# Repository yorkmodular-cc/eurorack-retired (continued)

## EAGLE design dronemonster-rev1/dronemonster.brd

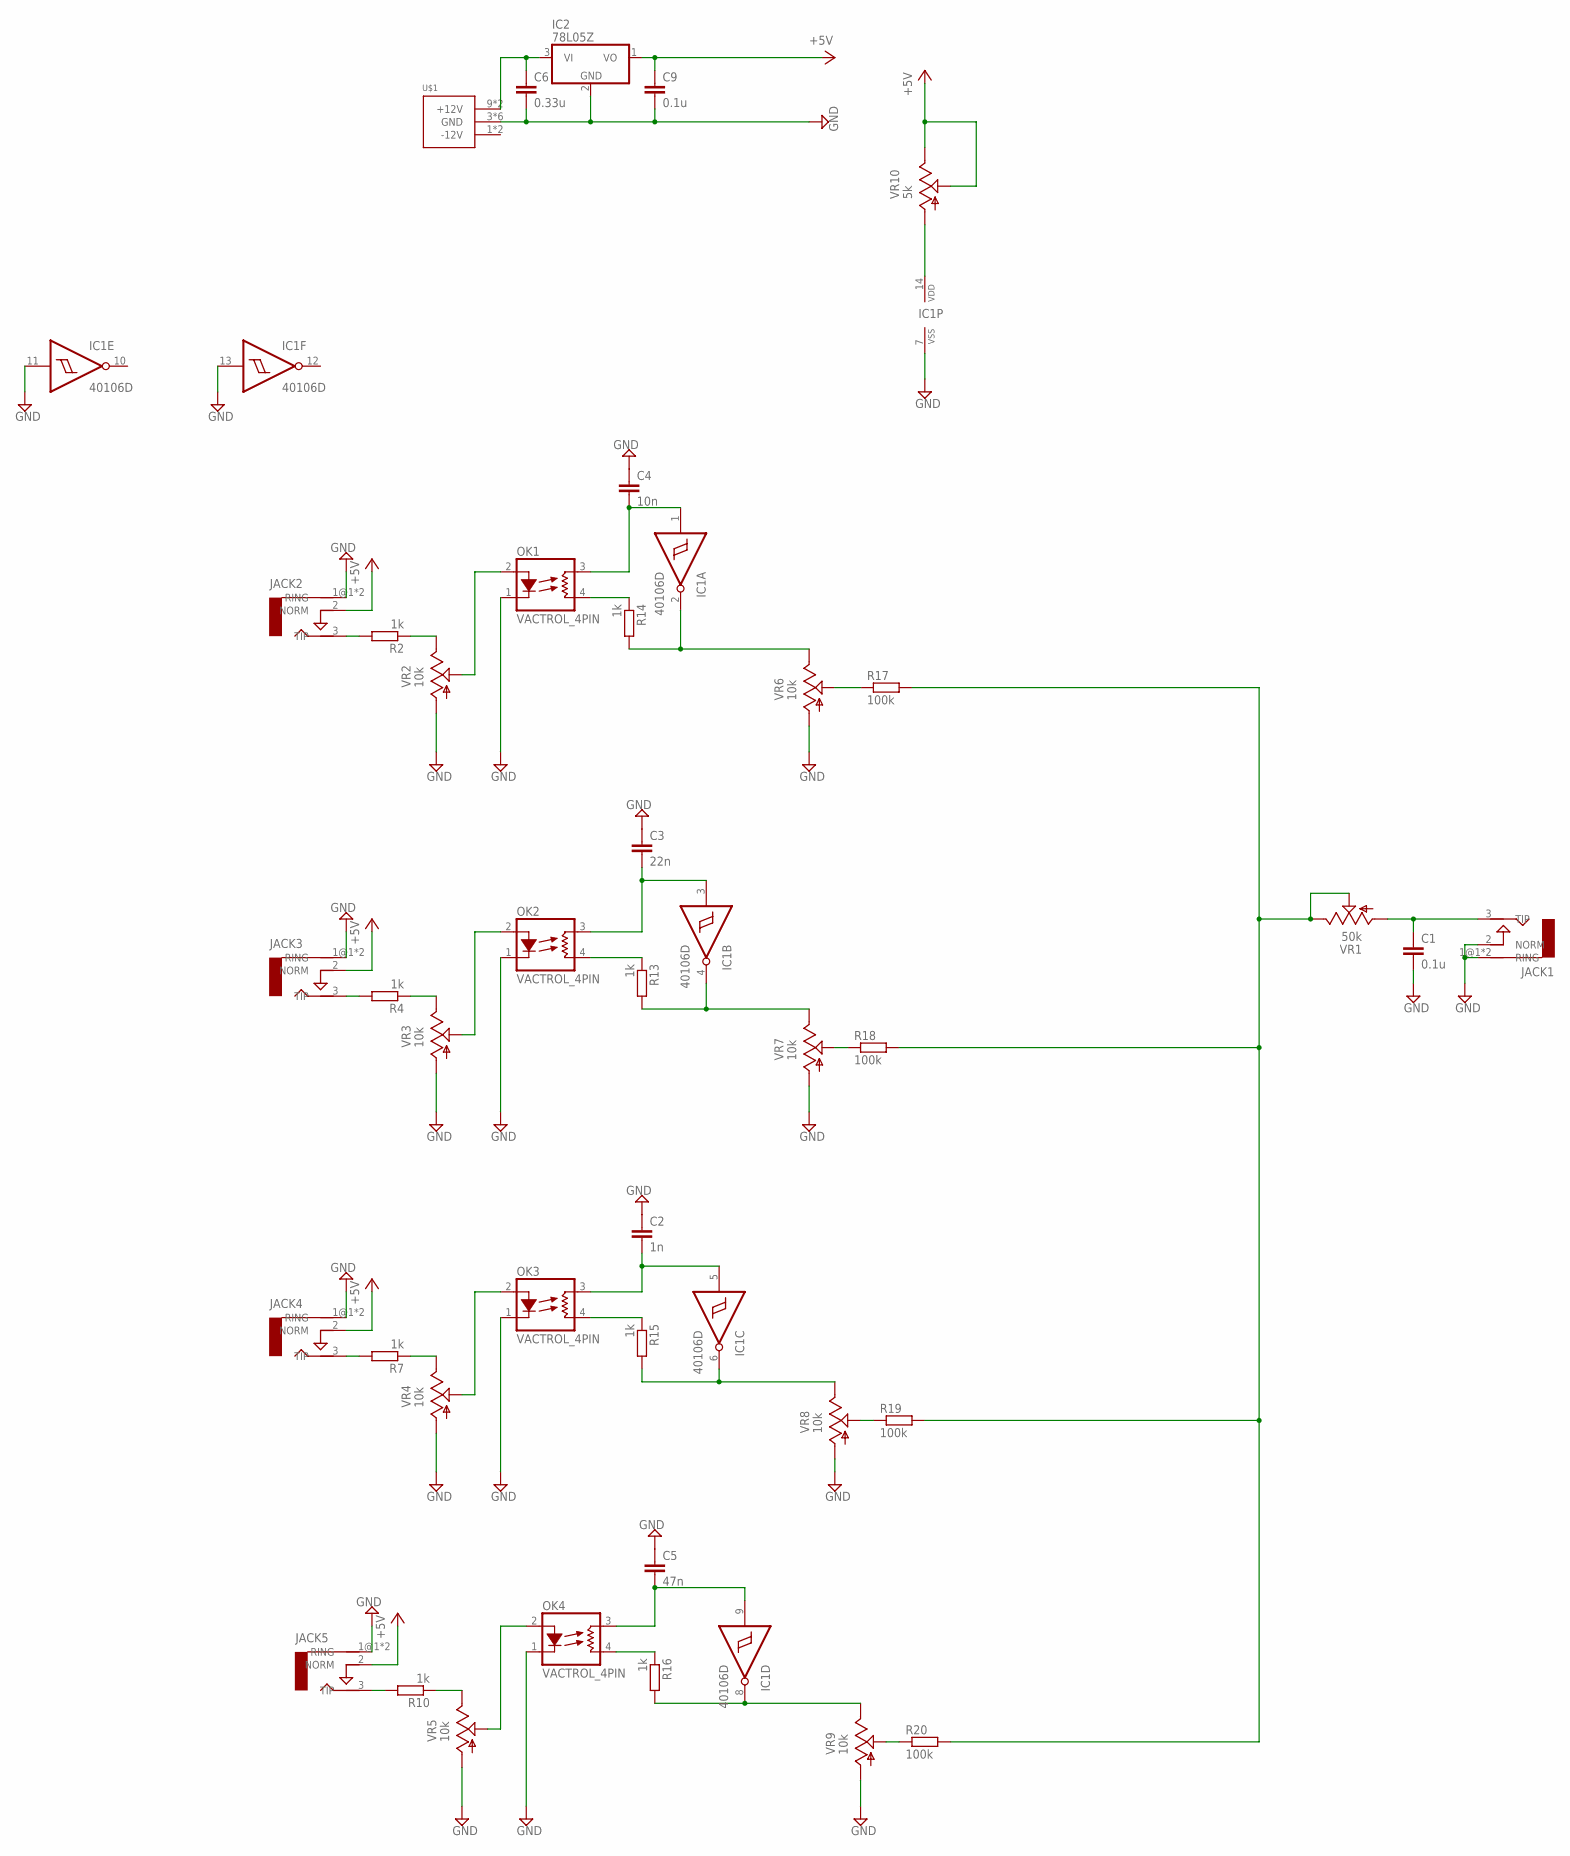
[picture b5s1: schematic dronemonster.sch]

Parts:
C1: 0.1u; C050-025X075
C2: 1n; C050-025X075
C3: 22n; C050-025X075
C4: 10n; C050-025X075
C5: 47n; C050-025X075
C6: 0.33u; C0805
C9: 0.1u; C0805
IC1: 40106D; SO14
IC2: 78L05Z; TO92
JACK1, JACK2, JACK3, JACK4, JACK5: AUDIO-JACKERTHENVAR; ERTHENVAR-JACK
OK1, OK2, OK3, OK4: VACTROL_4PIN; VACTROL_4PIN_VTL5C
R2, R4, R7, R10, R13, R14, R15, R16: 1k; R0805
R17, R18, R19, R20: 100k; R0805
U$1: POWER_SIMPLE10; POWER_10
VR1: 50k; 9MM_SNAP-IN_POT
VR2, VR3, VR4, VR5, VR6, VR7, VR8, VR9: 10k; 9MM_SNAP-IN_POT
VR10: 5k; 9MM_SNAP-IN_POT

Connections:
+5V: C9.1, IC2.1 (VO), JACK2.2 (NORM), JACK3.2 (NORM), JACK4.2 (NORM), JACK5.2 (NORM), VR10.2 (S), VR10.3 (E)
GND: C1.2, C2.1, C3.1, C4.1, C5.1, C6.2, C9.2, IC1.7 (VSS), IC1.11 (I), IC1.13 (I), IC2.2 (GND), JACK1.1@1 (RING), JACK1.1@2 (RING), JACK1.2 (NORM), JACK2.1@1 (RING), JACK2.1@2 (RING), JACK3.1@1 (RING), JACK3.1@2 (RING), JACK4.1@1 (RING), JACK4.1@2 (RING), JACK5.1@1 (RING), JACK5.1@2 (RING), OK1.1 (LED-), OK2.1 (LED-), OK3.1 (LED-), OK4.1 (LED-), U$1.3 (GND), U$1.4 (GND), U$1.5 (GND), U$1.6 (GND), U$1.7 (GND), U$1.8 (GND), VR2.1 (A), VR3.1 (A), VR4.1 (A), VR5.1 (A), VR6.1 (A), VR7.1 (A), VR8.1 (A), VR9.1 (A)
unnamed: C1.1, JACK1.3 (TIP), VR1.1 (A)
unnamed: IC1.14 (VDD), VR10.1 (A)
unnamed: JACK2.3 (TIP), R2.2
unnamed: OK1.2 (LED+), VR2.2 (S)
unnamed: R2.1, VR2.3 (E)
unnamed: R4.1, VR3.3 (E)
unnamed: JACK3.3 (TIP), R4.2
unnamed: OK2.2 (LED+), VR3.2 (S)
unnamed: R7.1, VR4.3 (E)
unnamed: JACK4.3 (TIP), R7.2
unnamed: OK3.2 (LED+), VR4.2 (S)
unnamed: R10.1, VR5.3 (E)
unnamed: JACK5.3 (TIP), R10.2
unnamed: OK4.2 (LED+), VR5.2 (S)
unnamed: R20.1, VR9.2 (S)
unnamed: R19.1, VR8.2 (S)
unnamed: OK4.4 (RES2), R16.1
unnamed: IC1.8 (O), R16.2, VR9.3 (E)
unnamed: C5.2, IC1.9 (I), OK4.3 (RES1)
unnamed: OK3.4 (RES2), R15.1
unnamed: IC1.6 (O), R15.2, VR8.3 (E)
unnamed: C2.2, IC1.5 (I), OK3.3 (RES1)
unnamed: OK2.4 (RES2), R13.1
unnamed: IC1.4 (O), R13.2, VR7.3 (E)
unnamed: C3.2, IC1.3 (I), OK2.3 (RES1)
unnamed: OK1.4 (RES2), R14.1
unnamed: IC1.2 (O), R14.2, VR6.3 (E)
unnamed: C4.2, IC1.1 (I), OK1.3 (RES1)
unnamed: R18.1, VR7.2 (S)
unnamed: C6.1, IC2.3 (VI), U$1.9 (+12V), U$1.10 (+12V)
unnamed: R17.1, VR6.2 (S)
OSC4: R17.2, R18.2, R19.2, R20.2, VR1.2 (S), VR1.3 (E)

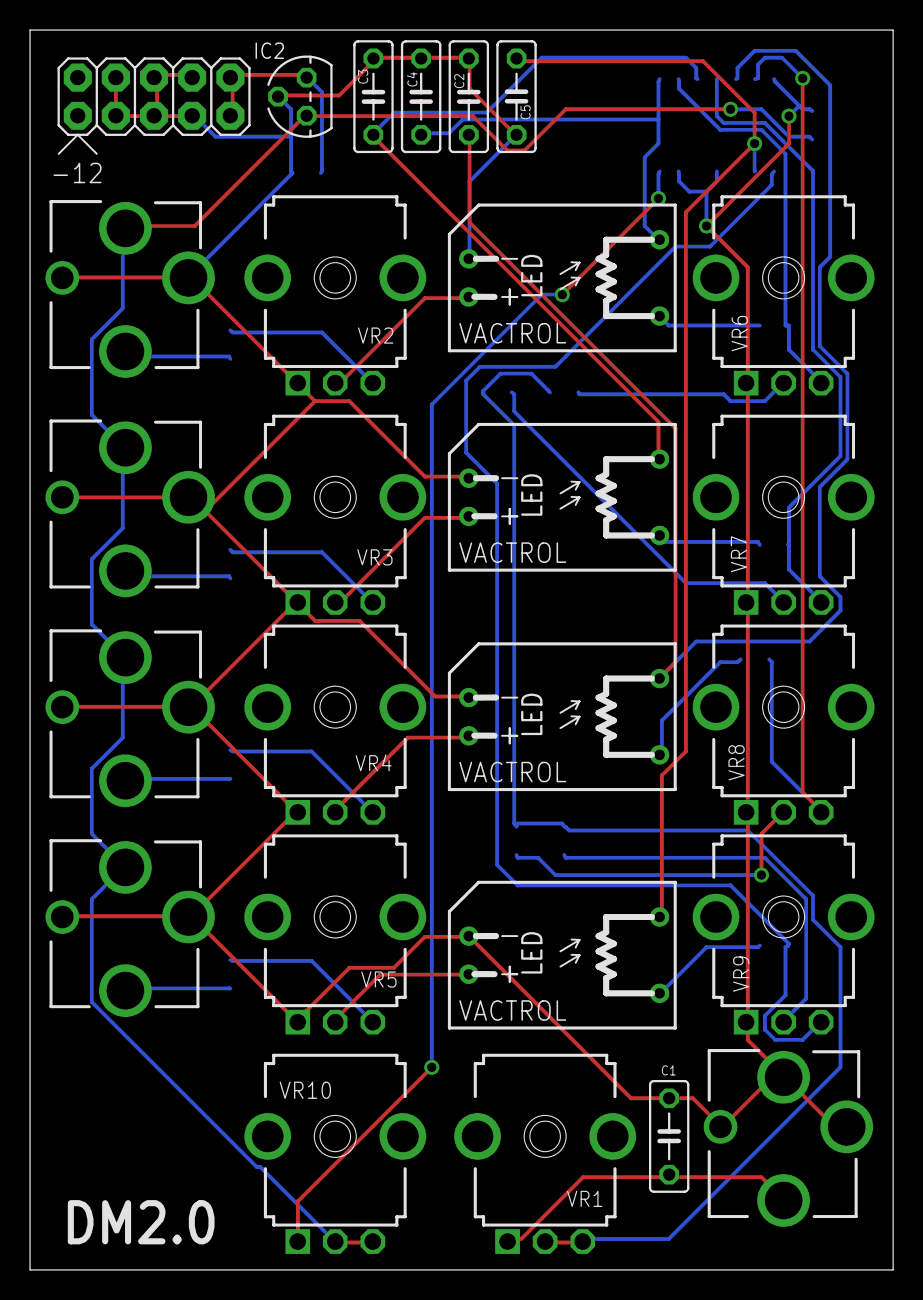
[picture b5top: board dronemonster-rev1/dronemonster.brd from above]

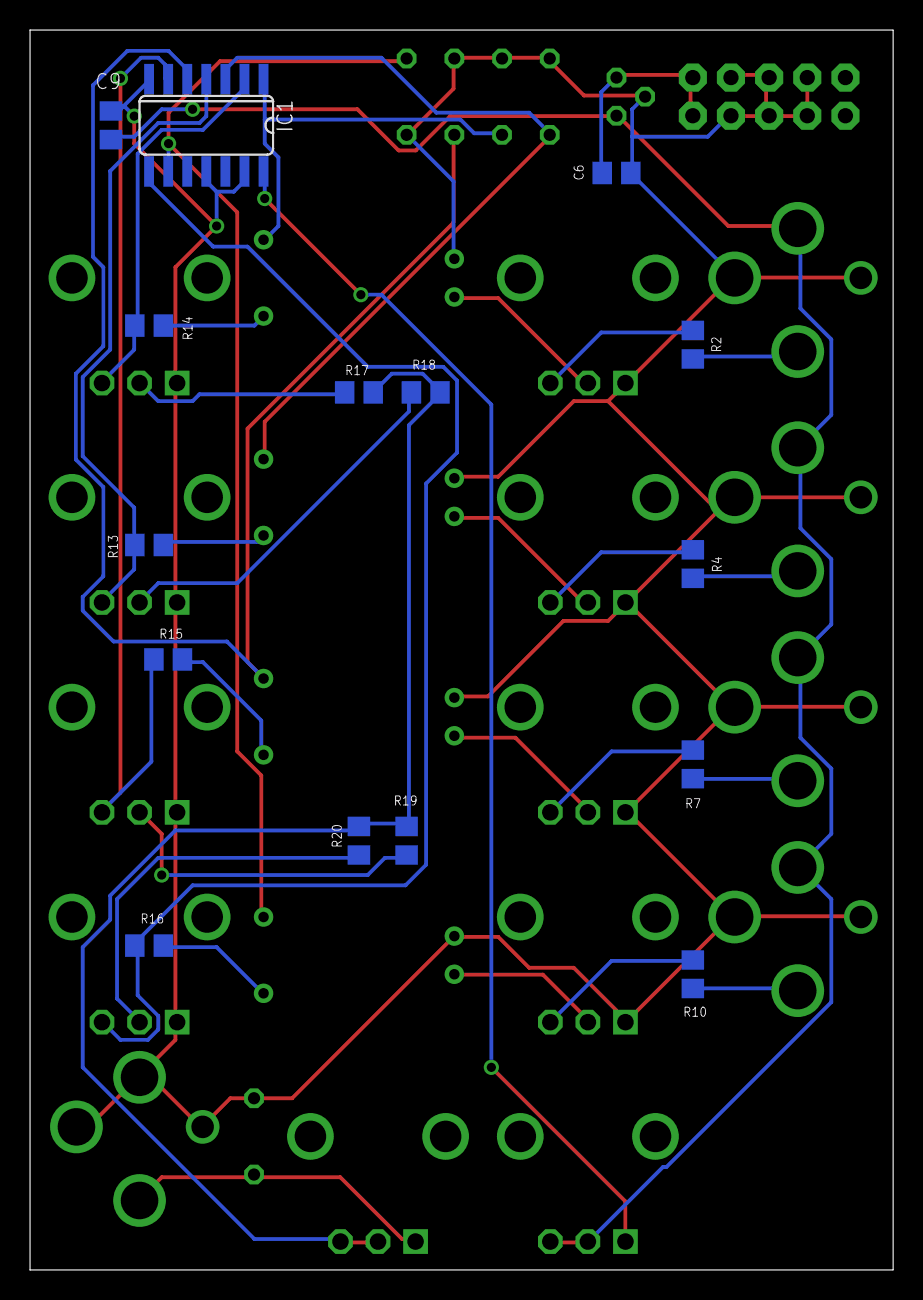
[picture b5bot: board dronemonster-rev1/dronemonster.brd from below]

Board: 2 copper layers, 57.5 x 82.5 mm, 41 parts (15 on the bottom side), 34 nets.

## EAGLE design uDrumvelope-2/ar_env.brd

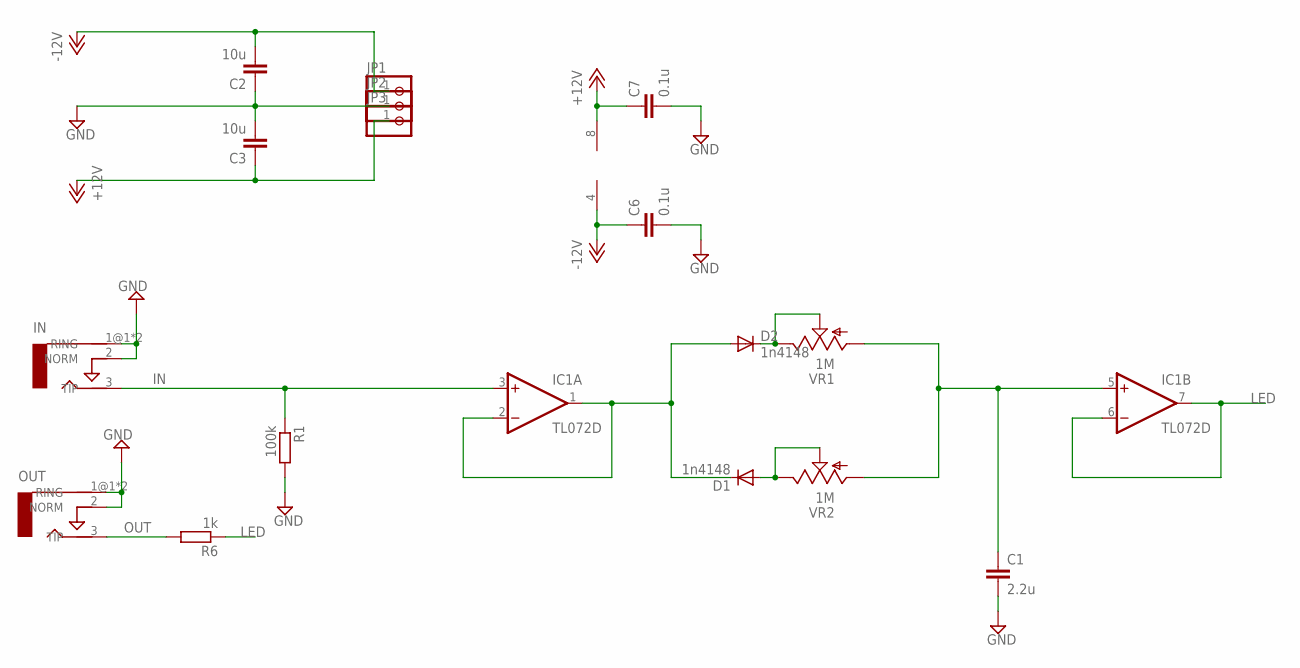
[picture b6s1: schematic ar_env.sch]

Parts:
C1: 2.2u; C0805
C2, C3: 10u; C0805
C6, C7: 0.1u; C0805
D1, D2: 1n4148; SOD323-W
IC1: TL072D; SO08
IN: AUDIO-JACKERTHENVAR; ERTHENVAR-JACK
JP1, JP2, JP3: PINHD-1X1; 1X01
OUT: AUDIO-JACKERTHENVAR; ERTHENVAR-JACK
R1: 100k; R0805
R6: 1k; R0805
VR1, VR2: 1M; 9MM_SNAP-IN_POT

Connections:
+12V: C3.1, C7.1, IC1.8 (V+), JP3.1
-12V: C2.2, C6.1, IC1.4 (V-), JP1.1
GND: C1.2, C2.1, C3.2, C6.2, C7.2, IN.1@1 (RING), IN.1@2 (RING), IN.2 (NORM), JP2.1, OUT.1@1 (RING), OUT.1@2 (RING), OUT.2 (NORM), R1.2
IN: IC1.3 (+IN), IN.3 (TIP), R1.1
LED: IC1.6 (-IN), IC1.7 (OUT), R6.1
unnamed: D2.C, VR1.2 (S), VR1.3 (E)
unnamed: D1.A, VR2.2 (S), VR2.3 (E)
unnamed: D1.C, D2.A, IC1.1 (OUT), IC1.2 (-IN)
unnamed: C1.1, IC1.5 (+IN), VR1.1 (A), VR2.1 (A)
OUT: OUT.3 (TIP), R6.2

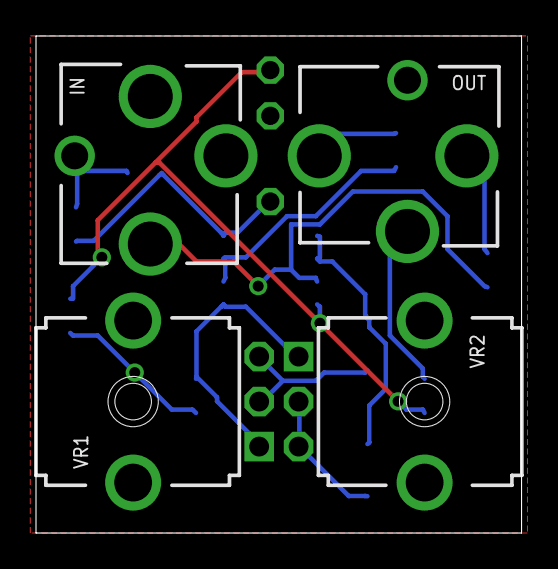
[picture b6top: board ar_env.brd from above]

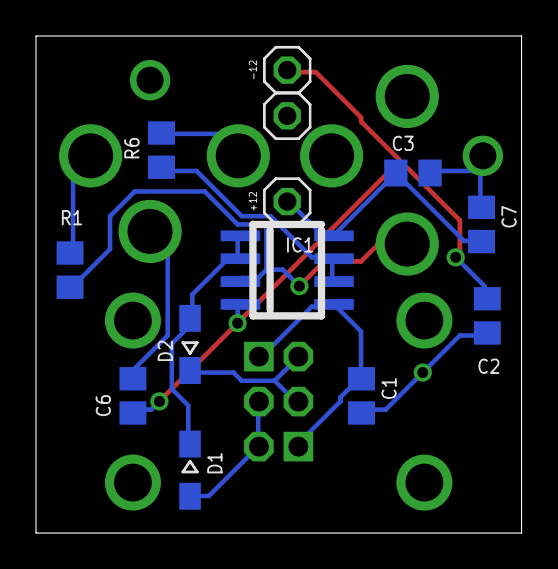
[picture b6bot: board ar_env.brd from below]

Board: 2 copper layers, 27.0 x 27.6 mm, 17 parts (13 on the bottom side), 10 nets.

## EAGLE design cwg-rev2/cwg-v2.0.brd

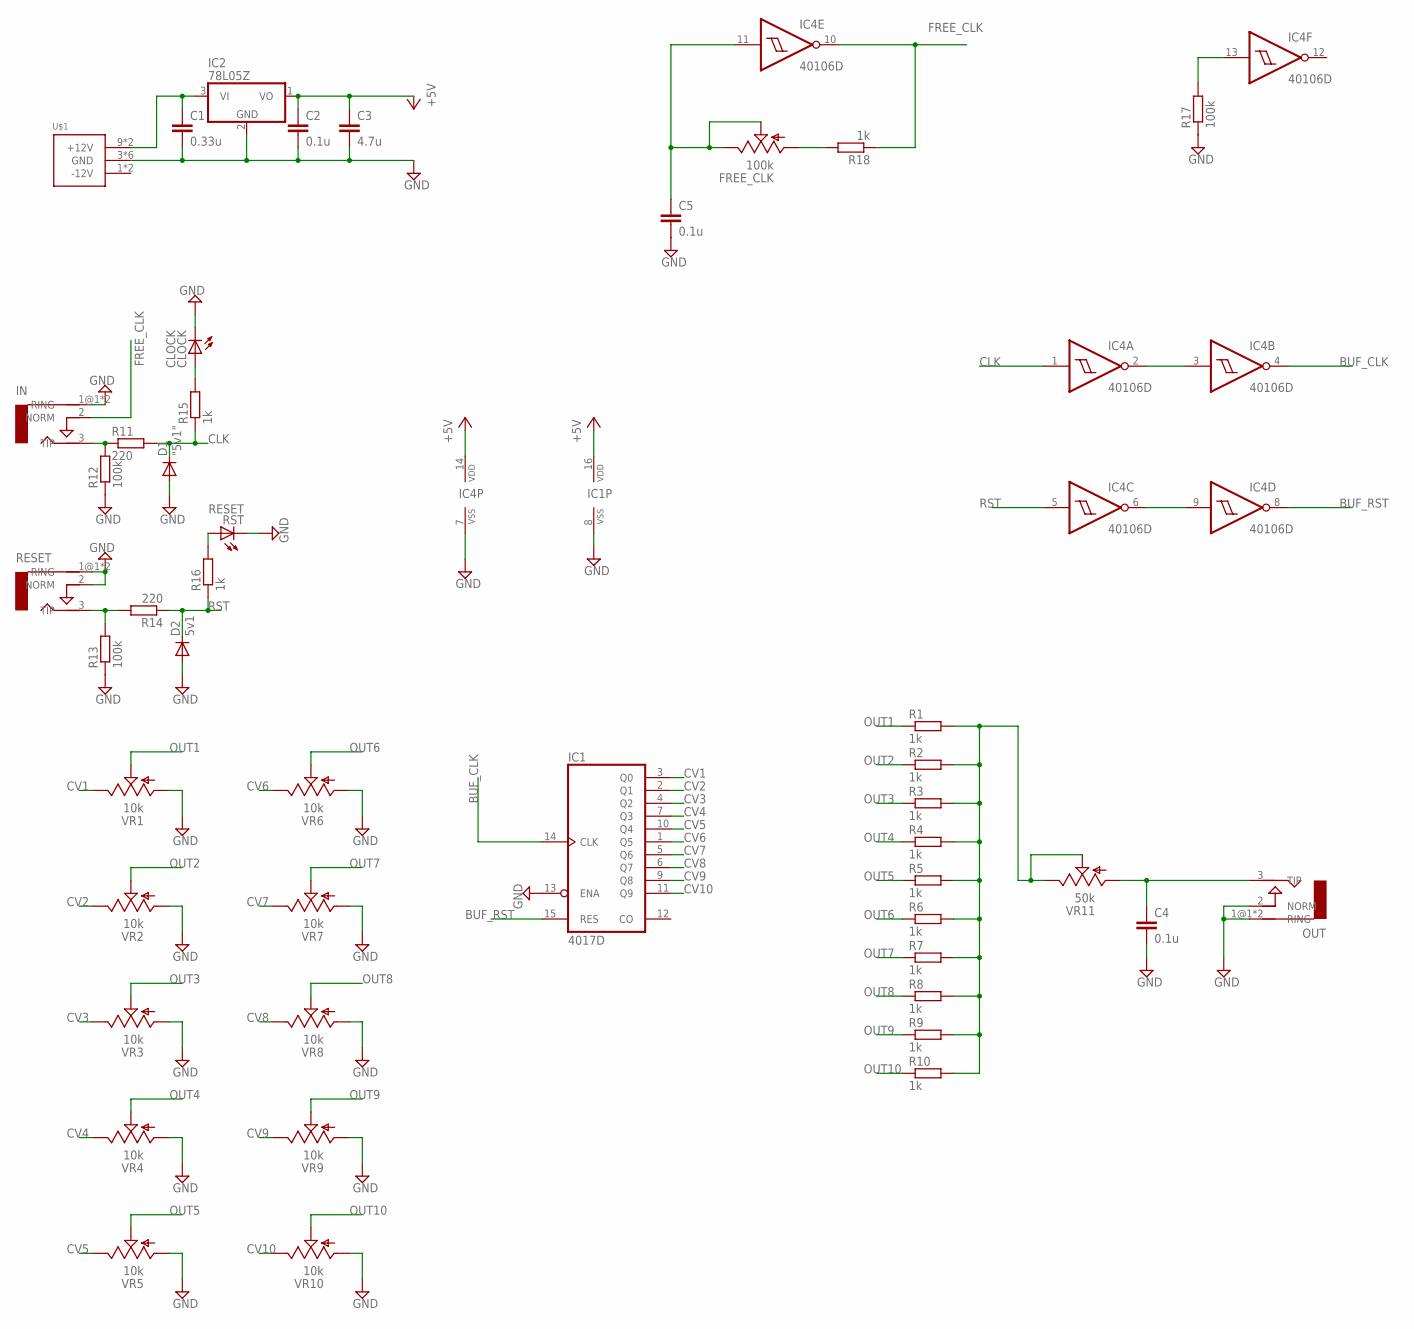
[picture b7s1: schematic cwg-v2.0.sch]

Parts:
C1: 0.33u; C0805
C2, C5: 0.1u; C0805
C3: 4.7u; C0805
C4: 0.1u; C050-025X075
CLOCK: CLOCK; CHIP-LED0805
D1: "5v1"; D-2.5
D2: 5v1; D-2.5
FREE_CLK: 100k; 9MM_SNAP-IN_POT
IC1: 4017D; SO16
IC2: 78L05Z; TO92
IC4: 40106D; SO14
IN: IN; ERTHENVAR-JACK
OUT: OUT; ERTHENVAR-JACK
R1, R2, R3, R4, R5, R6, R7, R8, R9, R10, R15, R16, R18: 1k; R0805
R11, R14: 220; R0805
R12, R13, R17: 100k; R0805
RESET: RESET; ERTHENVAR-JACK
RST: RESET; CHIP-LED0805
U$1: POWER_SIMPLE10; POWER_10
VR1, VR2, VR3, VR4, VR5, VR6, VR7, VR8, VR9, VR10: 10k; 9MM_SNAP-IN_POT
VR11: 50k; 9MM_SNAP-IN_POT

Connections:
+5V: C2.1, C3.1, IC1.16 (VDD), IC2.1 (VO), IC4.14 (VDD)
BUF_CLK: IC1.14 (CLK), IC4.4 (O)
BUF_RST: IC1.15 (RES), IC4.8 (O)
CLK: D1.C, IC4.1 (I), R11.2, R15.1
CV1: IC1.3 (Q0), VR1.3 (E)
CV2: IC1.2 (Q1), VR2.3 (E)
CV3: IC1.4 (Q2), VR3.3 (E)
CV4: IC1.7 (Q3), VR4.3 (E)
CV5: IC1.10 (Q4), VR5.3 (E)
CV6: IC1.1 (Q5), VR6.3 (E)
CV7: IC1.5 (Q6), VR7.3 (E)
CV8: IC1.6 (Q7), VR8.3 (E)
CV9: IC1.9 (Q8), VR9.3 (E)
CV10: IC1.11 (Q9), VR10.3 (E)
FREECLK: C5.1, FREE_CLK.2 (S), FREE_CLK.3 (E), IC4.11 (I)
FREE_CLK: IC4.10 (O), IN.2 (NORM), R18.1
GND: C1.2, C2.2, C3.2, C4.2, C5.2, CLOCK.C, D1.A, D2.A, IC1.8 (VSS), IC1.13 (ENA), IC2.2 (GND), IC4.7 (VSS), IN.1@1 (RING), IN.1@2 (RING), OUT.1@1 (RING), OUT.1@2 (RING), OUT.2 (NORM), R12.1, R13.1, R17.1, RESET.1@1 (RING), RESET.1@2 (RING), RESET.2 (NORM), RST.C, U$1.3 (GND), U$1.4 (GND), U$1.5 (GND), U$1.6 (GND), U$1.7 (GND), U$1.8 (GND), VR1.1 (A), VR2.1 (A), VR3.1 (A), VR4.1 (A), VR5.1 (A), VR6.1 (A), VR7.1 (A), VR8.1 (A), VR9.1 (A), VR10.1 (A)
unnamed: IN.3 (TIP), R11.1, R12.2
unnamed: CLOCK.A, R15.2
unnamed: IC4.2 (O), IC4.3 (I)
unnamed: R13.2, R14.2, RESET.3 (TIP)
unnamed: R16.2, RST.A
unnamed: C4.1, OUT.3 (TIP), VR11.1 (A)
unnamed: IC4.6 (O), IC4.9 (I)
unnamed: IC4.13 (I), R17.2
unnamed: C1.1, IC2.3 (VI), U$1.9 (+12V), U$1.10 (+12V)
unnamed: FREE_CLK.1 (A), R18.2
unnamed: R1.2, R2.2, R3.2, R4.2, R5.2, R6.2, R7.2, R8.2, R9.2, R10.2, VR11.2 (S), VR11.3 (E)
OUT1: R1.1, VR1.2 (S)
OUT2: R2.1, VR2.2 (S)
OUT3: R3.1, VR3.2 (S)
OUT4: R4.1, VR4.2 (S)
OUT5: R5.1, VR5.2 (S)
OUT6: R6.1, VR6.2 (S)
OUT7: R7.1, VR7.2 (S)
OUT8: R8.1, VR8.2 (S)
OUT9: R9.1, VR9.2 (S)
OUT10: R10.1, VR10.2 (S)
RST: D2.C, IC4.5 (I), R14.1, R16.1

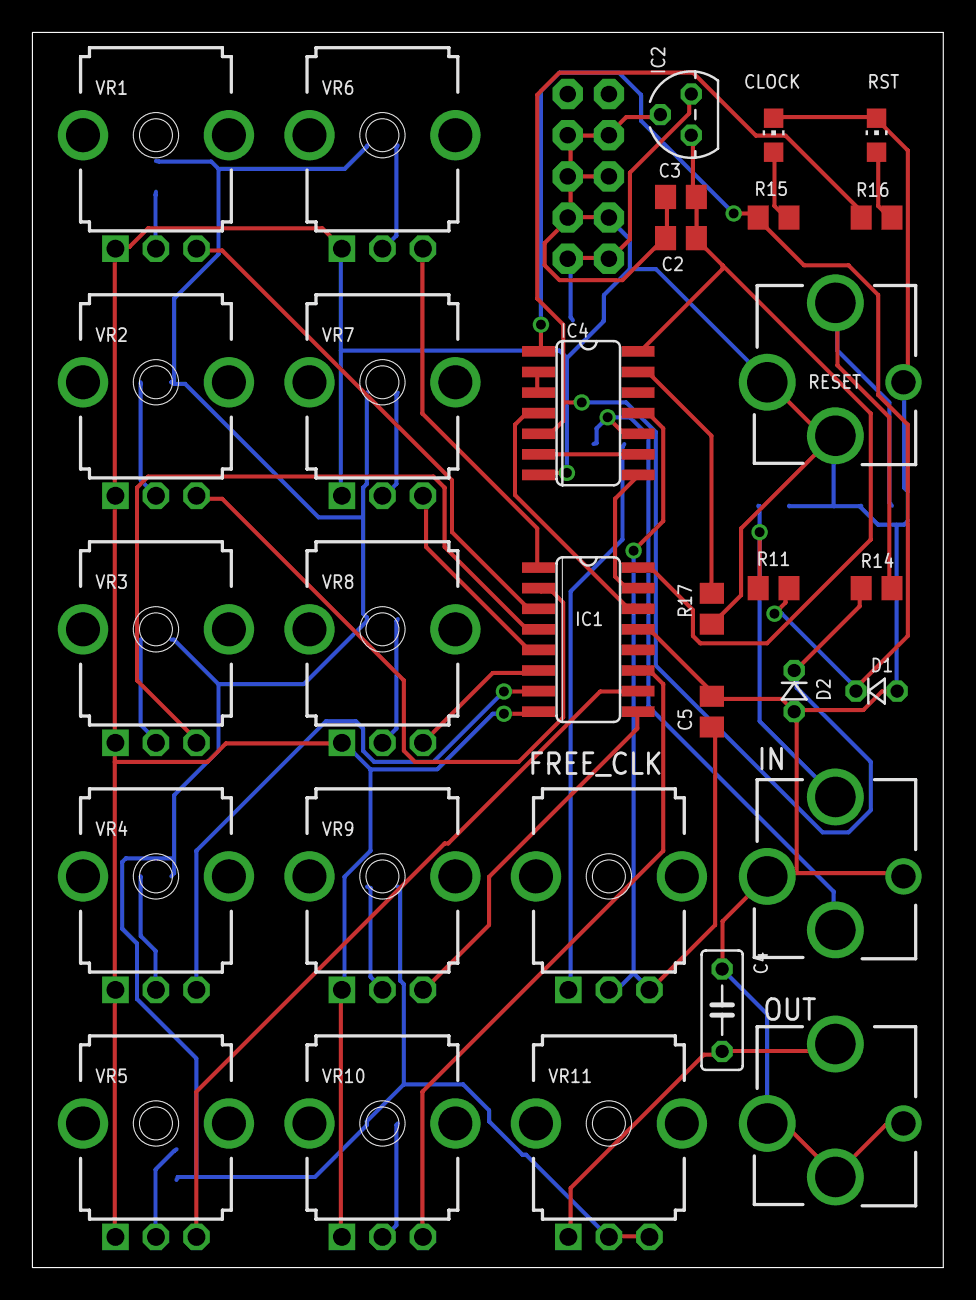
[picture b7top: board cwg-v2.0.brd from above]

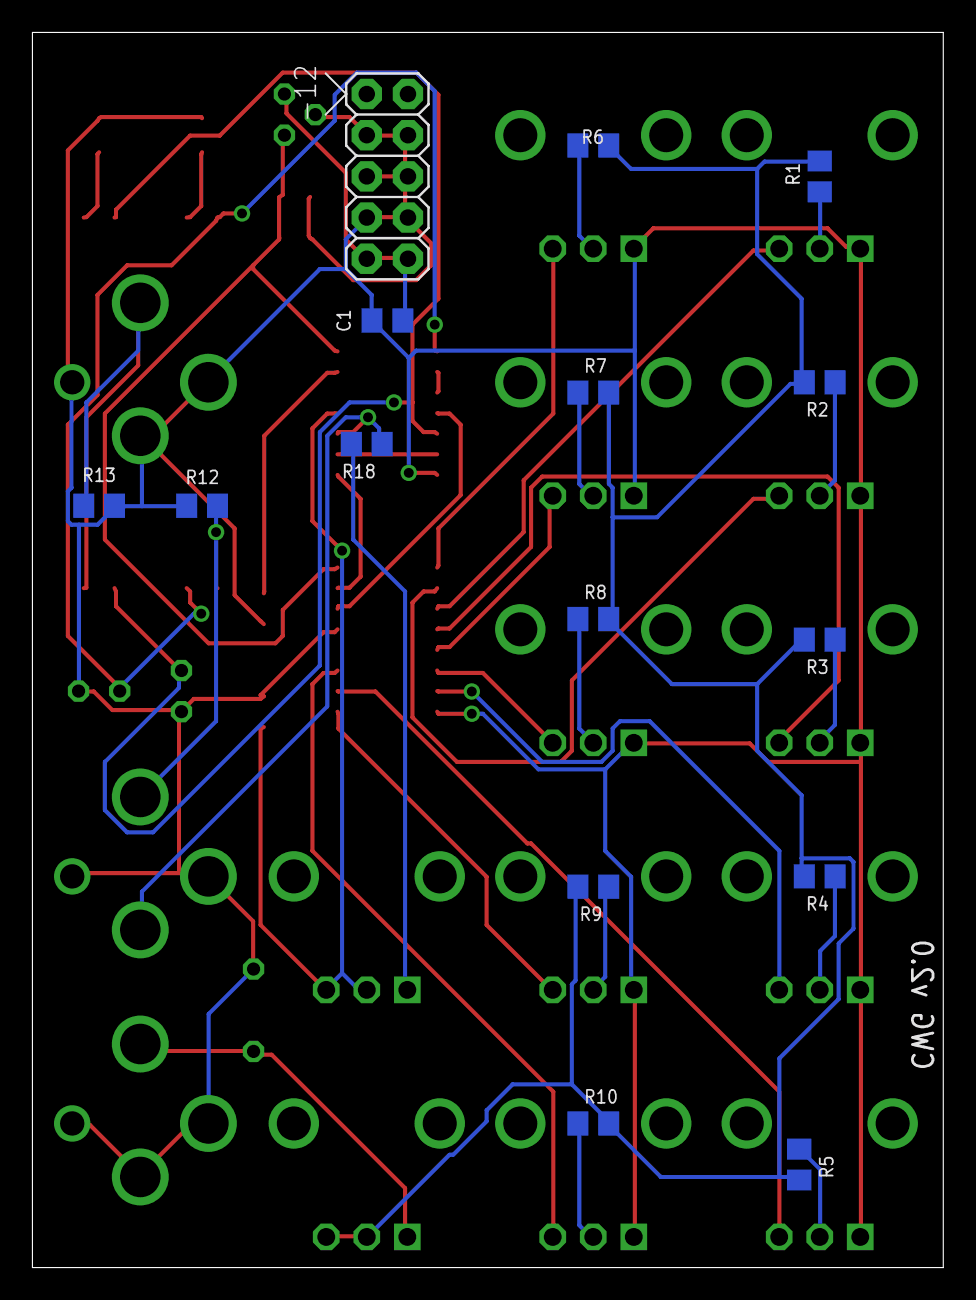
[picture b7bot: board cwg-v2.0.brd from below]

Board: 2 copper layers, 56.2 x 76.2 mm, 46 parts (15 on the bottom side), 39 nets.

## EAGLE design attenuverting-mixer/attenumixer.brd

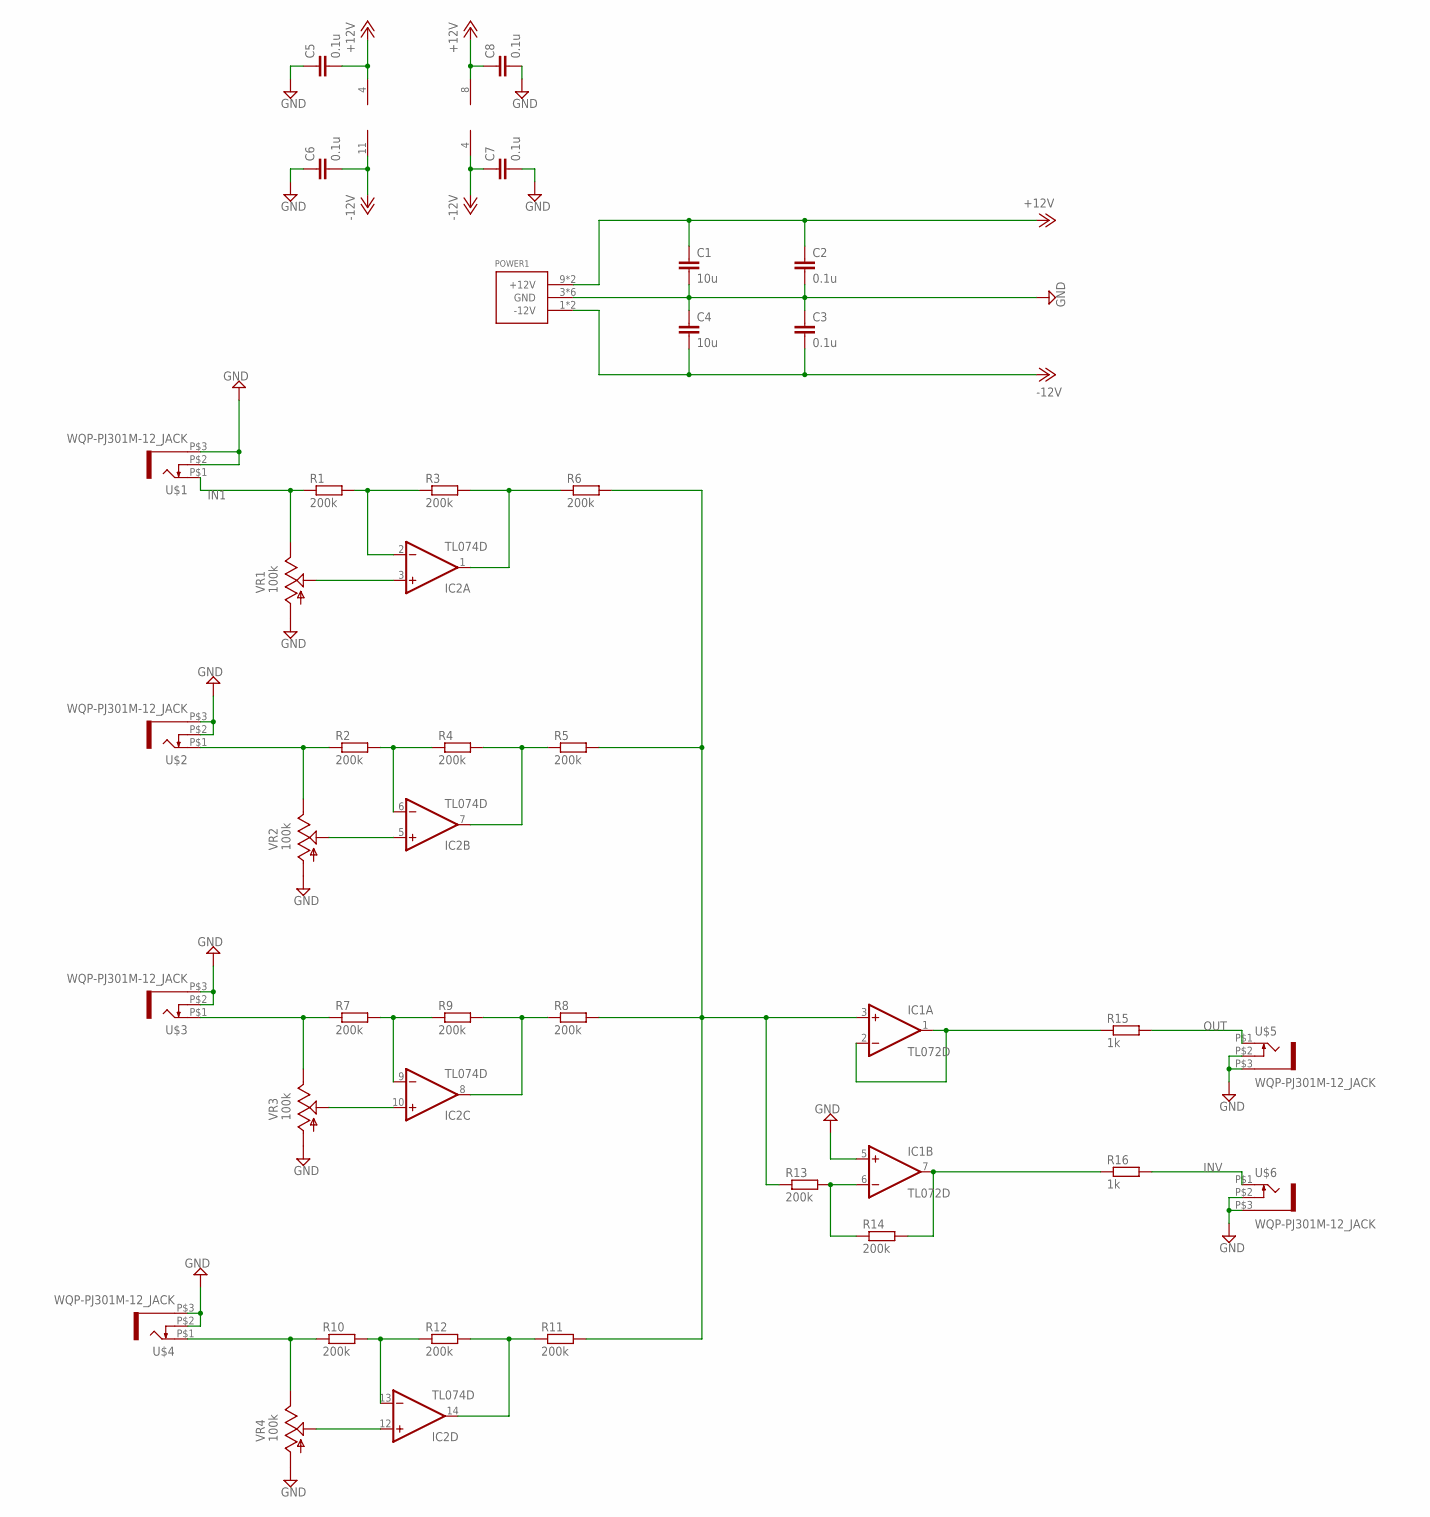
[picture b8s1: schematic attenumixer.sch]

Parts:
C1, C4: 10u; C0805
C2, C3, C5, C6, C7, C8: 0.1u; C0805
IC1: TL072D; SO08
IC2: TL074D; SO14
POWER1: POWER_SIMPLE10; POWER_10
R1, R2, R3, R4, R5, R6, R7, R8, R9, R10, R11, R12, R13, R14: 200k; R0805
R15, R16: 1k; R0805
U$1, U$2, U$3, U$4, U$5, U$6: WQP-PJ301M-12_JACK
VR1, VR2, VR3, VR4: 100k; 9MM_SNAP-IN_POT

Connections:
+12V: C1.1, C2.1, C5.2, C8.1, IC1.8 (V+), IC2.4 (V+), POWER1.9 (+12V), POWER1.10 (+12V)
-12V: C3.2, C4.2, C6.2, C7.1, IC1.4 (V-), IC2.11 (V-), POWER1.1 (-12V), POWER1.2 (-12V)
GND: C1.2, C2.2, C3.1, C4.1, C5.1, C6.1, C7.2, C8.2, IC1.5 (+IN), POWER1.3 (GND), POWER1.4 (GND), POWER1.5 (GND), POWER1.6 (GND), POWER1.7 (GND), POWER1.8 (GND), U$1.P$2 (3), U$1.P$3 (1), U$2.P$2 (3), U$2.P$3 (1), U$3.P$2 (3), U$3.P$3 (1), U$4.P$2 (3), U$4.P$3 (1), U$5.P$2 (3), U$5.P$3 (1), U$6.P$2 (3), U$6.P$3 (1), VR1.1 (A), VR2.1 (A), VR3.1 (A), VR4.1 (A)
IN1: R1.1, U$1.P$1 (2), VR1.3 (E)
INV: R16.2, U$6.P$1 (2)
unnamed: IC2.3 (+IN), VR1.2 (S)
unnamed: IC2.5 (+IN), VR2.2 (S)
unnamed: IC2.7 (OUT), R4.2, R5.1
unnamed: R2.1, U$2.P$1 (2), VR2.3 (E)
unnamed: IC2.1 (OUT), R3.2, R6.1
unnamed: IC2.2 (-IN), R1.2, R3.1
unnamed: IC2.10 (+IN), VR3.2 (S)
unnamed: IC2.6 (-IN), R2.2, R4.1
unnamed: IC1.1 (OUT), IC1.2 (-IN), R15.1
unnamed: IC2.8 (OUT), R8.1, R9.2
unnamed: R7.1, U$3.P$1 (2), VR3.3 (E)
unnamed: IC2.9 (-IN), R7.2, R9.1
unnamed: IC1.7 (OUT), R14.2, R16.1
unnamed: IC2.12 (+IN), VR4.2 (S)
unnamed: IC2.14 (OUT), R11.1, R12.2
unnamed: R10.1, U$4.P$1 (2), VR4.3 (E)
unnamed: IC2.13 (-IN), R10.2, R12.1
unnamed: IC1.3 (+IN), R5.2, R6.2, R8.2, R11.2, R13.1
unnamed: IC1.6 (-IN), R13.2, R14.1
OUT: R15.2, U$5.P$1 (2)

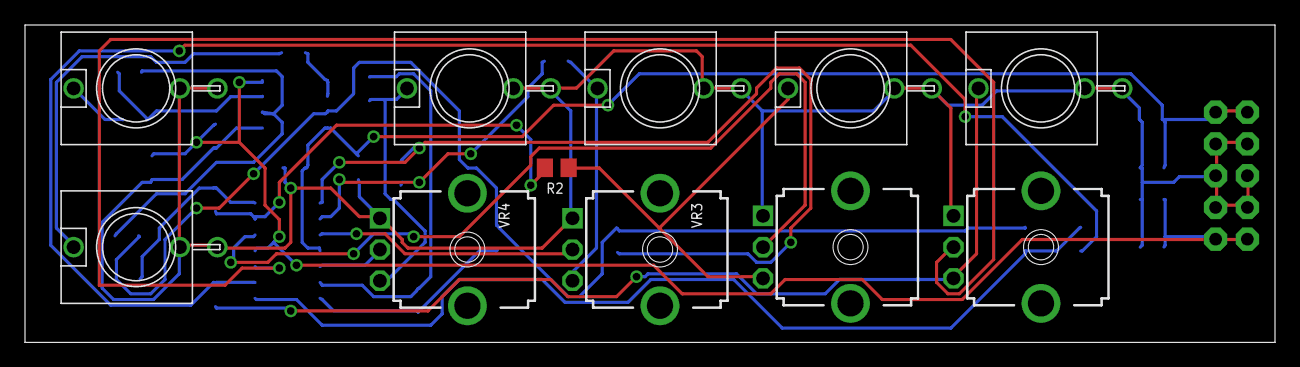
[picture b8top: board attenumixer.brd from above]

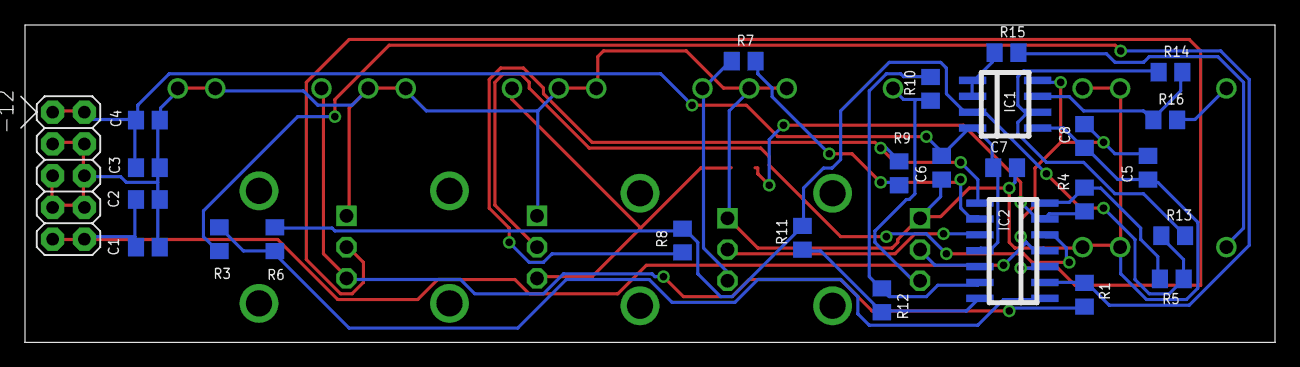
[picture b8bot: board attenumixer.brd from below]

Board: 2 copper layers, 100.0 x 25.4 mm, 37 parts (26 on the bottom side), 25 nets.

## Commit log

2018-01-11 1U diode OR
2018-01-11 4-bit R2R DAC
2018-01-11 Dual signal booster
2018-01-11 Buffered mult
2018-01-11 Dual glide buffer
2018-01-11 Dual offset generator
2018-01-11 Mixer/multiple
2018-01-11 OptoThing ghetto VCA - revision 2
2018-01-11 White noise generator
2018-01-11 Unity-gain mixer
2018-01-11 Resonant low-pass Sallen-Key filter
2018-01-11 Multi-feedback resonant high-pass filter
2018-01-11 Multiple-feedback resonant high-pass filter
2018-01-11 Sample and Hold - revision 1
2018-01-11 OptoThing - revision 1
2018-01-11 Multi-feedback resonant bandpass filter
2018-01-11 Multi-feedback resonant bandpass filter - revision 2
2018-01-11 XO106 drone generator - revision 1
2018-01-11 Multi-feedback resonant high-pass filter - revision 2
2018-01-11 Removed old .hg files
2018-01-11 Resonant low-pass Sallen-Key filter - revision 2
2018-01-11 Drumvelope2 - AR generator
2018-01-11 Quad voltage source
2018-01-11 FREAQ filter - revision 3
2018-01-11 Sample and hold -revision 2
2018-01-11 4069 resonant filter
2018-01-11 FREAQ filter - revision 2
2018-01-11 Unity-gain mixer/multiple
2018-01-11 Remove old .hg files
2018-01-11 Some panel files added.
2018-05-14 1U sample and hold
2018-05-14 XO106 revision 3
2018-05-14 MiniVAC
2018-05-14 Quad attenuator rev.2
2018-05-14 DualVerter rev.1
2018-05-14 Resonant bandpass filter rev 3
2018-05-14 Resonant high pass filter rev 3
2018-05-14 Dronebox
2018-05-14 Attenuverting mixer
2018-05-14 More retired stuff
2018-05-14 ADSR and divider
